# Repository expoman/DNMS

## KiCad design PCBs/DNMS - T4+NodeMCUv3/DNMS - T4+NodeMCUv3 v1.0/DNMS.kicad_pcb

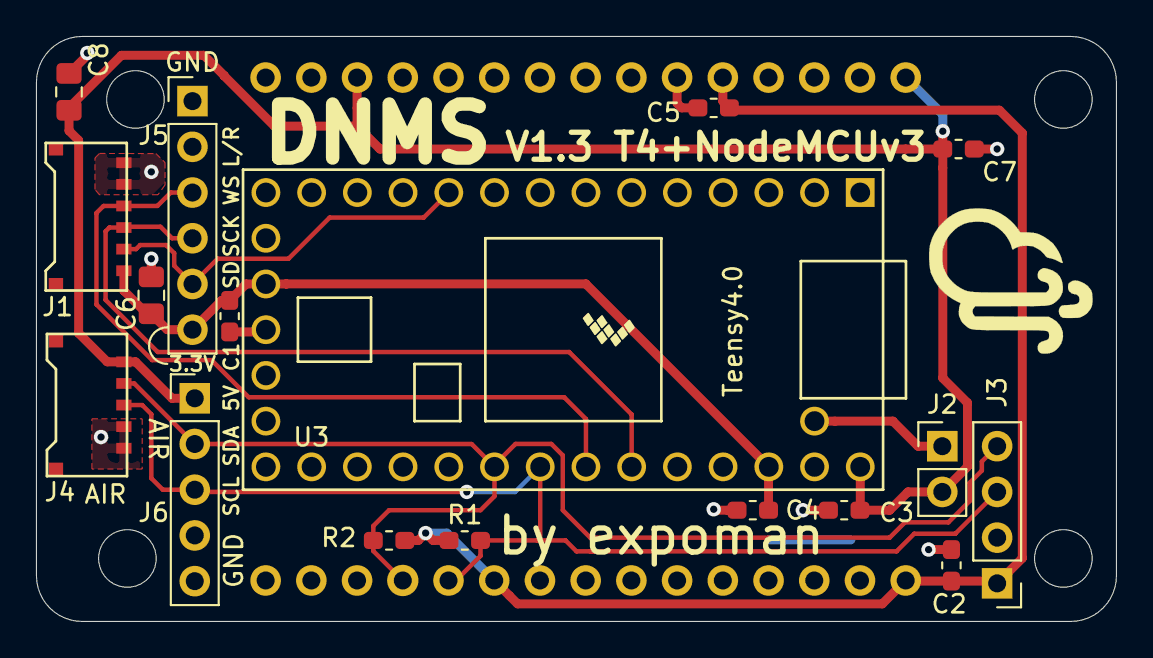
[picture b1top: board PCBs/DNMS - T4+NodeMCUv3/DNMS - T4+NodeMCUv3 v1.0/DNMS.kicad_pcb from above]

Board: 2 copper layers, 60.0 x 32.5 mm, 22 parts (1 on the bottom side), 10 nets.

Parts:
C1, C2, C3, C4, C5, C7: 100nF; C_0603_1608Metric_Pad1.05x0.95mm_HandSolder
C6, C8: 10uF; C_0805_2012Metric_Pad1.15x1.40mm_HandSolder
J1: Conn_01x06; molex_pico-ezmate_781715006_1x06_P1.20mm_Horizontal
J2: Conn_01x02; PinHeader_1x02_P2.54mm_Vertical
J3: Conn_01x04; PinHeader_1x04_P2.54mm_Vertical
J4: Conn_01x05; Molex_Pico-EZmate_78171-0005_1x05-1MP_P1.20mm_Horizontal
J5: Conn_01x06; PinHeader_1x06_P2.54mm_Vertical
J6: Conn_01x05; PinHeader_1x05_P2.54mm_Vertical
R1, R2: 4k7; R_0603_1608Metric_Pad1.05x0.95mm_HandSolder
REF1, REF1#2, REF1#3, REF1#4: MountingHole_2.7mm_M2.5
U2: NodeMCU V3; NodeMCU-LoLinV3
U3: Teensy4.0; Teensy40

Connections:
+3.3VP: C1.1, C4.1, C6.1, J1.6, J5.6, U3.16, U3.31
+3V3: C2.1, C5.1, J3.1, R1.1, R2.1, U2.11, U2.16, U2.25
+5V: C3.1, C7.1, C8.1, J2.2, J4.1, J6.1, U2.3, U2.15, U3.33
GND: C1.2, C2.2, C3.2, C4.2, C5.2, C6.2, C7.2, C8.2, J1.1, J1.2, J3.2, J4.4, J4.5, J5.1, J5.2, J6.4, J6.5, U2.10, U2.14, U2.17, U2.24, U3.1, U3.17, U3.32
unnamed: J2.1, U3.34
SCK: J1.4, J5.4, U3.28
SCL: J3.3, J4.3, J6.3, R1.2, U2.26, U3.26
SD: J1.5, J5.5, U3.10
SDA: J3.4, J4.2, J6.2, R2.2, U2.27, U3.25
WS: J1.3, J5.3, U3.27

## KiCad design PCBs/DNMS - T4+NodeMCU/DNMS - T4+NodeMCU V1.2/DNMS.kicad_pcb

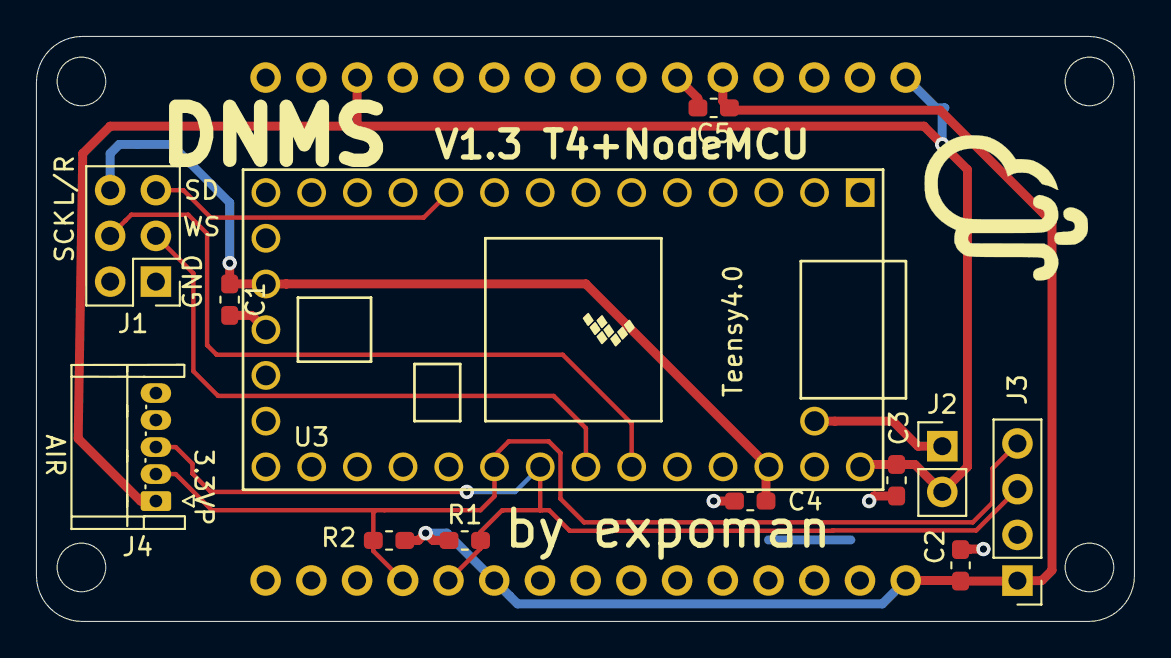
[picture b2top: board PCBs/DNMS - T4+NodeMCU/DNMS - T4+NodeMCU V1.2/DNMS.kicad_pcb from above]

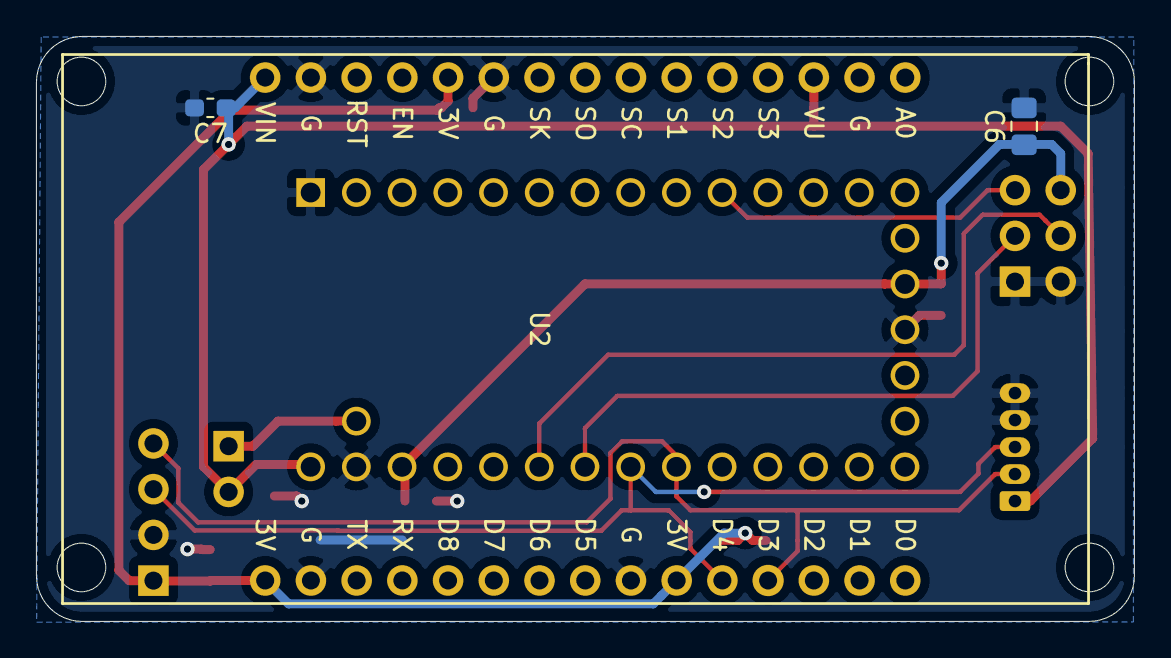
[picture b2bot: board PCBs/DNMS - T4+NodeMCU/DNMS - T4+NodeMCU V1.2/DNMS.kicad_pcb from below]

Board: 2 copper layers, 61.0 x 32.5 mm, 19 parts (3 on the bottom side), 10 nets.

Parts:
C1, C2, C3, C4, C5, C7: 100nF; C_0603_1608Metric_Pad1.05x0.95mm_HandSolder
C6: 10uF; C_0805_2012Metric_Pad1.15x1.40mm_HandSolder
J1: Conn_02x03_Odd_Even; PinHeader_2x03_P2.54mm_Vertical
J2: Conn_01x02; PinHeader_1x02_P2.54mm_Vertical
J3: Conn_01x04; PinHeader_1x04_P2.54mm_Vertical
J4: Conn_01x05; JST_ZH_S5B-EH_1x05_P1.50mm_Horizontal
R1, R2: 4k7; R_0603_1608Metric_Pad1.05x0.95mm_HandSolder
REF1, REF1#2, REF1#3, REF1#4: MountingHole_2.7mm_M2.5
U2: NodeMCU V3; NodeMCU-LoLinV3
U3: Teensy4.0; Teensy40

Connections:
+3.3VP: C1.1, C4.1, C6.1, J1.6, U3.16, U3.31
+3V3: C2.1, C5.1, J3.1, R1.1, R2.1, U2.11, U2.16, U2.25
+5V: C3.1, C7.1, J2.2, J4.1, U2.3, U2.15, U3.33
GND: C1.2, C2.2, C3.2, C4.2, C5.2, C6.2, C7.2, J1.1, J1.2, J3.2, J4.4, J4.5, U2.10, U2.14, U2.17, U2.24, U3.1, U3.17, U3.32
unnamed: J2.1, U3.34
SCK: J1.4, U3.28
SCL: J3.3, J4.3, R1.2, U2.26, U3.26
SD: J1.5, U3.10
SDA: J3.4, J4.2, R2.2, U2.27, U3.25
WS: J1.3, U3.27

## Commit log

2020-02-20 add my DNMS pcb
    uses only NodeMCUv3
    half of T4+NodeMcu
2020-02-21 move connectors
2020-02-24 change connector to mic to molex pico-ezmate
    move other connectors around
2020-02-27 add 2.54mm connector headers next to pico ezmate connectors
    for backwards compability
    moved text around and cleaned design
    added additional capcitors
2020-02-27 smaller changes to pcb
2020-03-02 smaller pcb changes
2020-03-03 move mounting holes
    increase diameter of holes to 3.2mm
2020-03-03 change/move text on silkscreen layer
2020-03-04 optimize few text labels
2020-03-04 move component
